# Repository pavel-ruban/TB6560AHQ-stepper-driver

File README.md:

#TB6560AHQ-stepper-driver
KiCAD project of stepper motor driver that is used to drive 1.6-1.7 A 2-phase stepper motors like NEMA-17 for CNC or 3D printers applications.

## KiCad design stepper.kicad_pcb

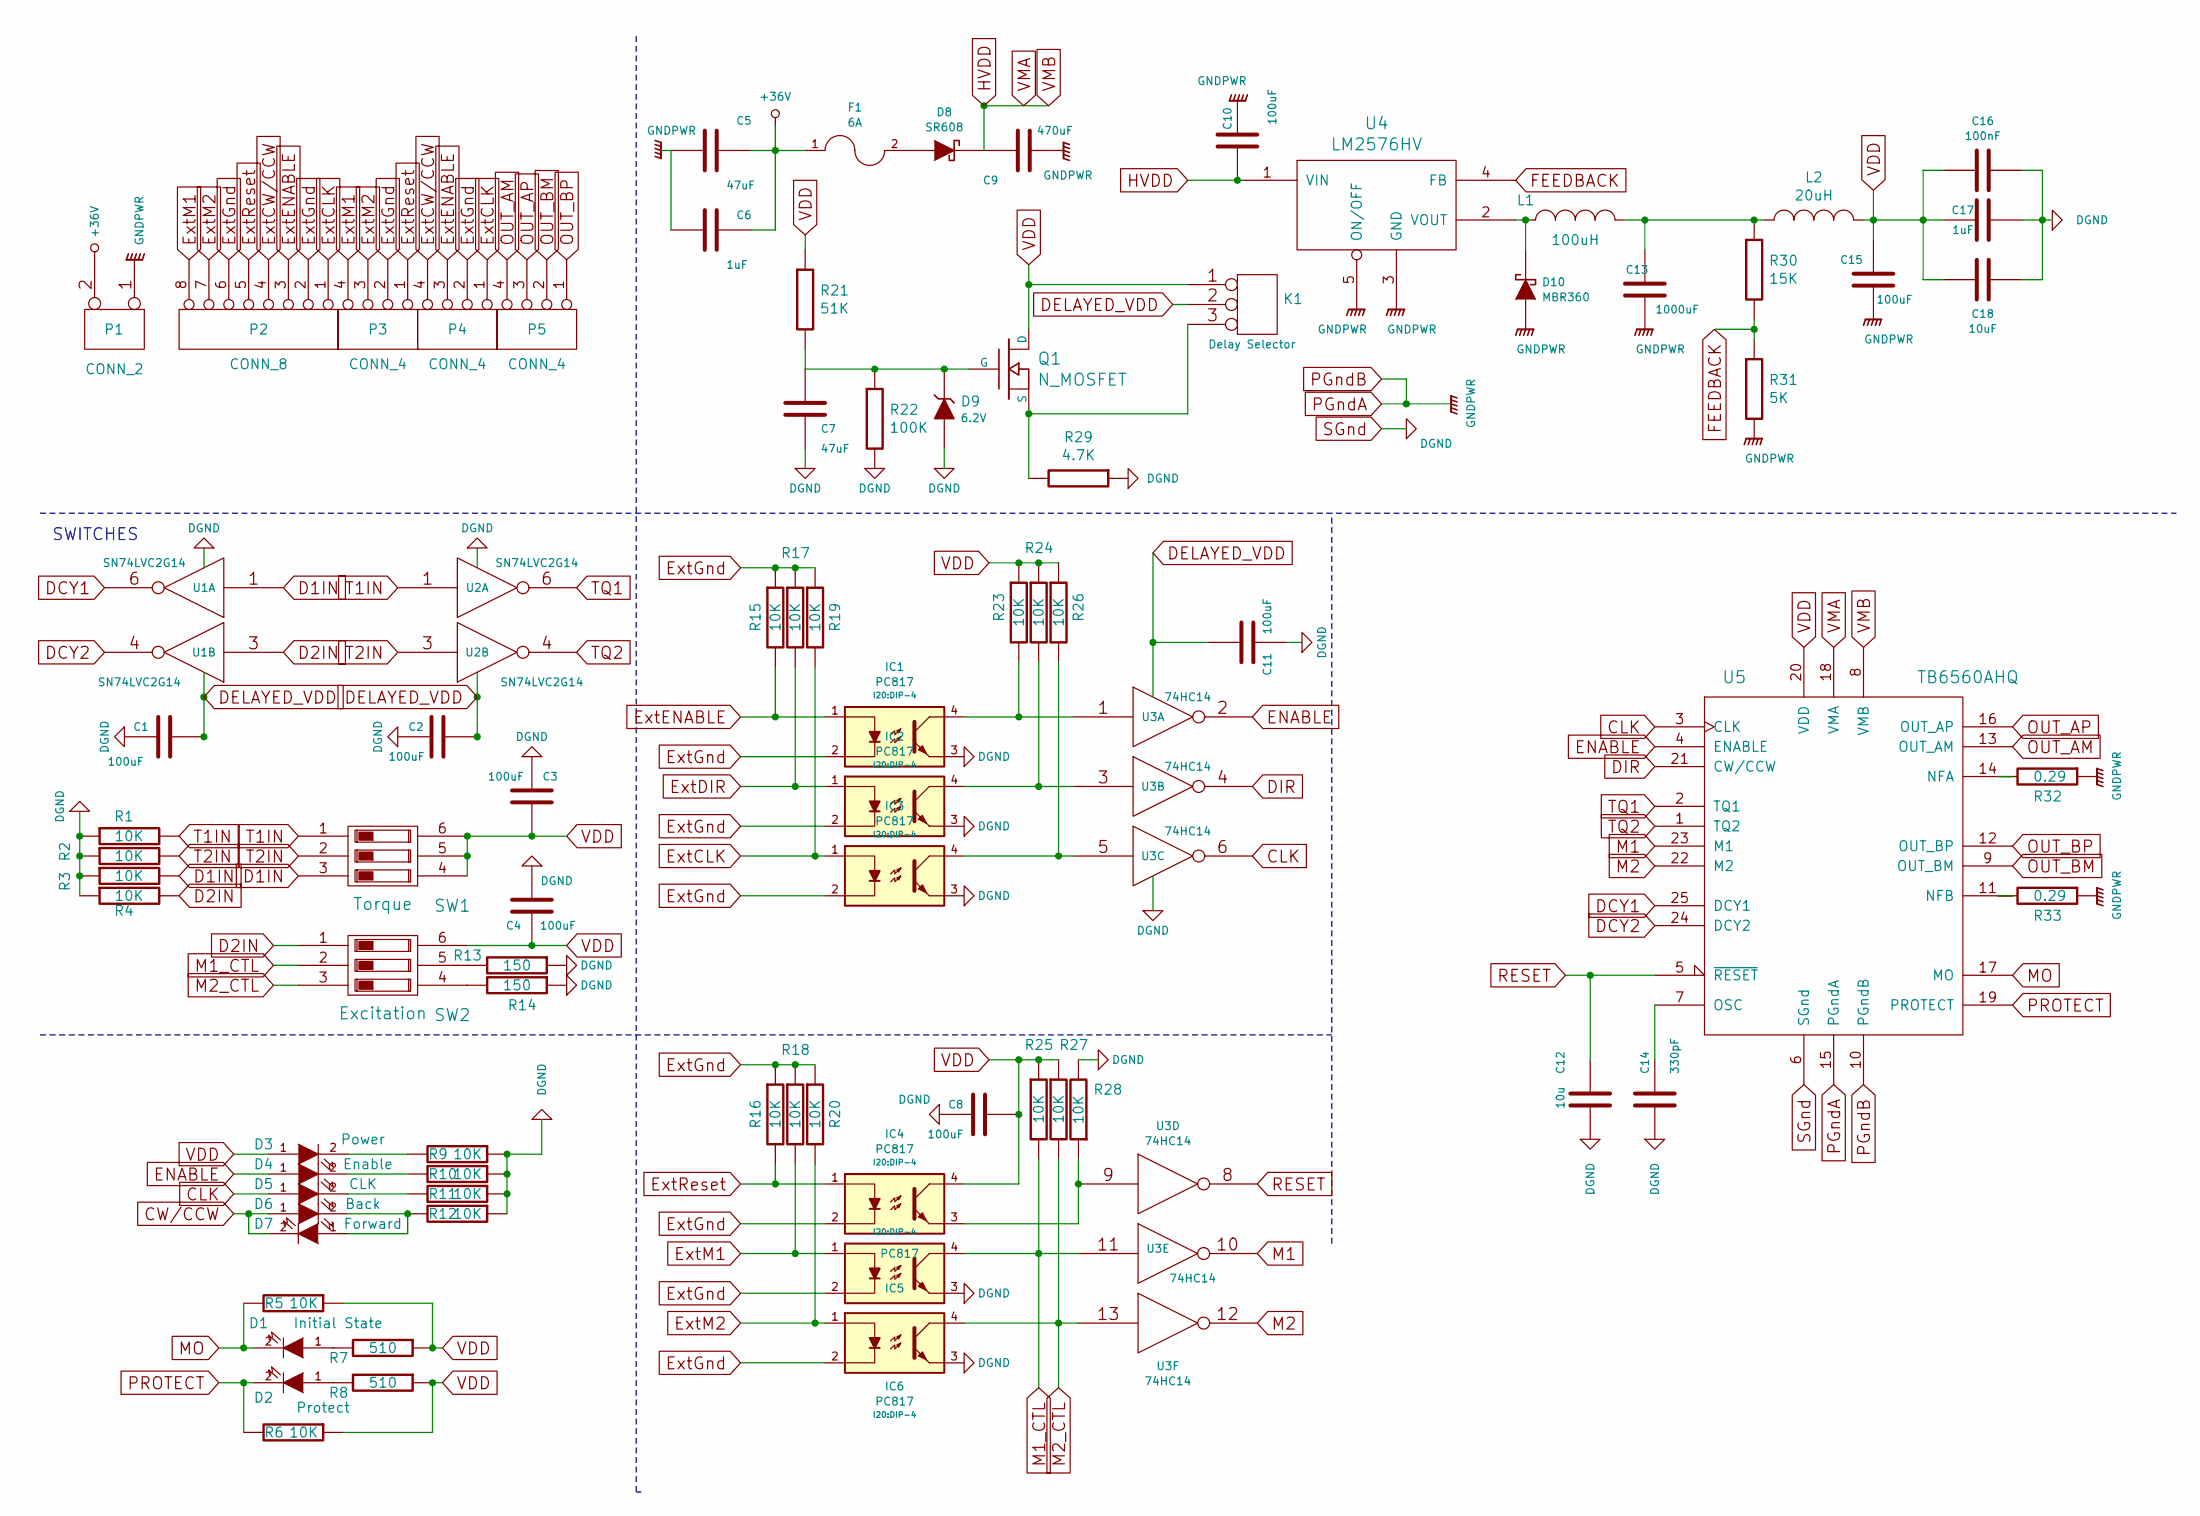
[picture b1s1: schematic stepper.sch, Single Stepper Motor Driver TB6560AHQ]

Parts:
C1, C2, C3, C4, C8, C11: 100uF; C_0805
C5, C7: 47uF; C_Radial_D6.3_L11.2_P2.5
C6: 1uF; C_Radial_D5_L11_P2.5
C9: 470uF; C_Radial_D10_L20_P5
C10, C15: 100uF; C_Radial_D8_L13_P3.8
C12: 10u; C_0805
C13: 1000uF; C_Radial_D10_L20_P5
C14: 330pF; C_0805
C16: 100nF; C_0805
C17: 1uF; C_0805
C18: 10uF; C_0805
D1: Initial State; LED_0805
D2: Protect; LED_0805
D3: Power; LED_0805
D4: Enable; LED_0805
D5: CLK; LED_0805
D6: Back; LED_0805
D7: Forward; LED_0805
D8: SR608; diode_r6
D9: 6.2V; MiniMELF_Standard
D10: MBR360; Diode_DO-201AD_Horizontal_RM15
F1: 6A; Fuseholder5x20_horiz_SemiClosed_Casing10x25mm
IC1, IC2, IC3, IC4, IC5, IC6: PC817; DIP-4
K1: Delay Selector; Pin_Header_Straight_1x03
L1: 100uH; L_Radial_D6.3_L11.2_P2.5
L2: 20uH; L_Radial_D6.3_L11.2_P2.5
P1: CONN_2; PhoenixContact_MSTBA-G_02x5.08mm_Angled
P2: CONN_8; Pin_Header_Straight_1x08
P3, P4: CONN_4; JST_XH_B04B-XH-A_04x2.50mm_Straight
P5: CONN_4; PhoenixContact_MSTBA-G_04x5.08mm_Angled
Q1: N_MOSFET; SOT-23
R1, R2, R3, R4, R5, R6, R9, R10, R11, R12, R15, R16, R17, R18, R19, R20, R23, R24, R25, R26, R27, R28: 10K; R_0805
R7, R8: 510; R_0805
R13, R14: 150; R_0805
R21: 51K; R_0805
R22: 100K; R_0805
R29: 4.7K; R_0805
R30: 15K; R_0805
R31: 5K; R_0805
R32, R33: 0.29; Resistor_Horizontal_RM15mm
SW1: Torque; DIPS-DS03
SW2: Excitation; DIPS-DS03
U1, U2: SN74LVC2G14; SOT-23-6
U3: 74HC14; SO14
U4: LM2576HV; Pentawatt_Neutral_Staggered_Verical_TO220-5-T05D
U5: TB6560AHQ; HZIP25_P_1_27_H

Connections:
+36V: C5.1, C6.1, F1.1, P1.2 (PM)
CLK: D5.1 (A), U3.6, U5.3 (CLK)
CW/CCW: D6.1 (A), D7.2 (K)
D1IN: R3.2, SW1.3, U1.1
D2IN: R4.2, SW2.1, U1.3
DCY1: U1.6, U5.25 (DCY1)
DCY2: U1.4, U5.24 (DCY2)
DELAYED_VDD: C1.2, C2.1, C11.2, K1.2 (PM), U1.5 (VCC), U2.5 (VCC), U3.14 (VCC)
DIR: U3.4, U5.21 (CW/CCW)
ENABLE: D4.1 (A), U3.2, U5.4 (ENABLE)
ExtCLK: IC3.1, P2.1, P4.1, R19.2
ExtCW/CCW: P2.4, P4.4
ExtDIR: IC2.1, R17.2
ExtENABLE: IC1.1, P2.3, P4.3, R15.2
ExtGnd: IC1.2, IC2.2, IC3.2, IC4.2, IC5.2, IC6.2, P2.2, P2.6, P3.2, P4.2, R15.1, R16.1, R17.1, R18.1, R19.1, R20.1
ExtM1: IC5.1, P2.8, P3.4, R18.2
ExtM2: IC6.1, P2.7, P3.3, R20.2
ExtReset: IC4.1, P2.5, P3.1, R16.2
FEEDBACK: R30.2, R31.1, U4.4 (FB)
HVDD: C9.1, C10.2, D8.2 (K), U4.1 (VIN), U5.8 (VMB), U5.18 (VMA)
M1: U3.10, U5.23 (M1)
M1_CTL: IC5.4, R25.2, SW2.2, U3.11
M2: U3.12, U5.22 (M2)
M2_CTL: IC6.4, R27.2, SW2.3, U3.13
MO: D1.2 (K), R5.2, U5.17 (MO)
unnamed: C7.2, D9.2 (K), Q1.1 (G), R21.2, R22.1
unnamed: C13.1, L1.2, L2.1, R30.1
unnamed: C14.1, U5.7 (OSC)
unnamed: D1.1 (A), R7.2
unnamed: D2.1 (A), R8.2
unnamed: D3.2 (K), R9.2
unnamed: D4.2 (K), R10.2
unnamed: D5.2 (K), R11.2
unnamed: D6.2 (K), D7.1 (A), R12.2
unnamed: D8.1 (A), F1.2
unnamed: D10.2 (K), L1.1, U4.2 (VOUT)
unnamed: IC1.4, R23.2, U3.1
unnamed: IC2.4, R24.2, U3.3
unnamed: IC3.4, R26.2, U3.5
unnamed: IC4.3, R28.1, U3.9
unnamed: K1.3, Q1.2 (S), R29.2
unnamed: R13.2, SW2.5
unnamed: R14.2, SW2.4
unnamed: R32.2, U5.14 (NFA)
unnamed: R33.2, U5.11 (NFB)
OUT_AM: P5.4, U5.13 (OUT_AM)
OUT_AP: P5.3, U5.16 (OUT_AP)
OUT_BM: P5.2, U5.9 (OUT_BM)
OUT_BP: P5.1, U5.12 (OUT_BP)
PGndA: C5.2, C6.2, C9.2, C10.1, C13.2, C15.2, D10.1 (A), P1.1, R31.2, R32.1, R33.1, U4.3 (GND), U4.5 (ON/OFF), U5.10 (PGndB), U5.15 (PGndA)
PROTECT: D2.2 (K), R6.2, U5.19 (PROTECT)
RESET: C12.1, U3.8, U5.5 (~RESET)
SGnd: C1.1, C2.2, C3.1, C4.2, C7.1, C8.1, C11.1, C12.2, C14.2, C16.2, C17.2, C18.2, D9.1 (A), IC1.3, IC2.3, IC3.3, IC5.3, IC6.3, R1.1, R2.1, R3.1, R4.1, R9.1, R10.1, R11.1, R12.1, R13.1, R14.1, R22.2, R28.2, R29.1, U1.2 (GND), U2.2 (GND), U3.7 (GND), U5.6 (SGnd)
T1IN: R1.2, SW1.1, U2.1
T2IN: R2.2, SW1.2, U2.3
TQ1: U2.6, U5.2 (TQ1)
TQ2: U2.4, U5.1 (TQ2)
VDD: C3.2, C4.1, C8.2, C15.1, C16.1, C17.1, C18.1, D3.1 (A), IC4.4, K1.1, L2.2, Q1.3 (D), R5.1, R6.1, R7.1, R8.1, R21.1, R23.1, R24.1, R25.1, R26.1, R27.1, SW1.4, SW1.5, SW1.6, SW2.6, U5.20 (VDD)

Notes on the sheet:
SWITCHES

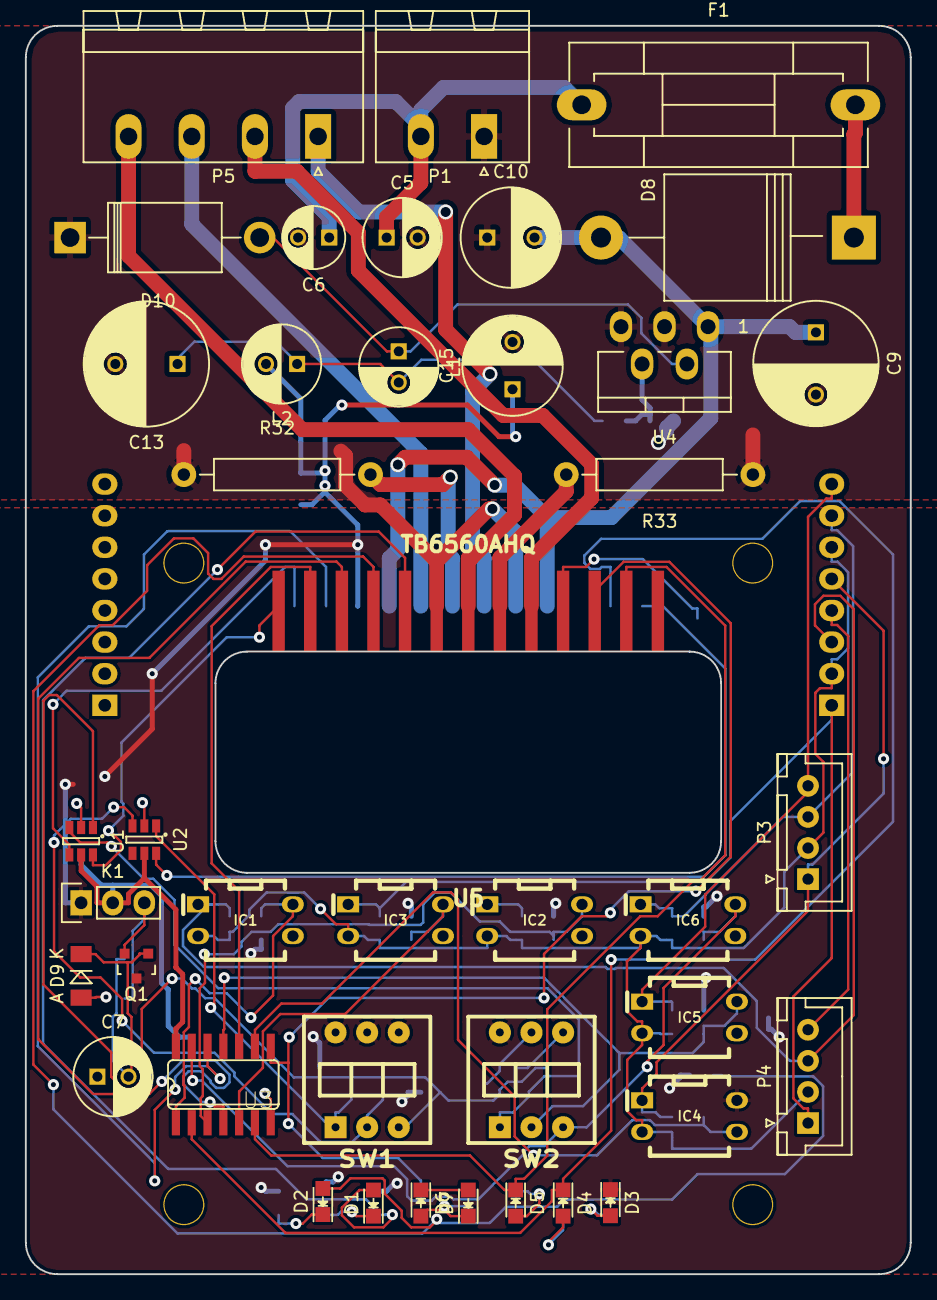
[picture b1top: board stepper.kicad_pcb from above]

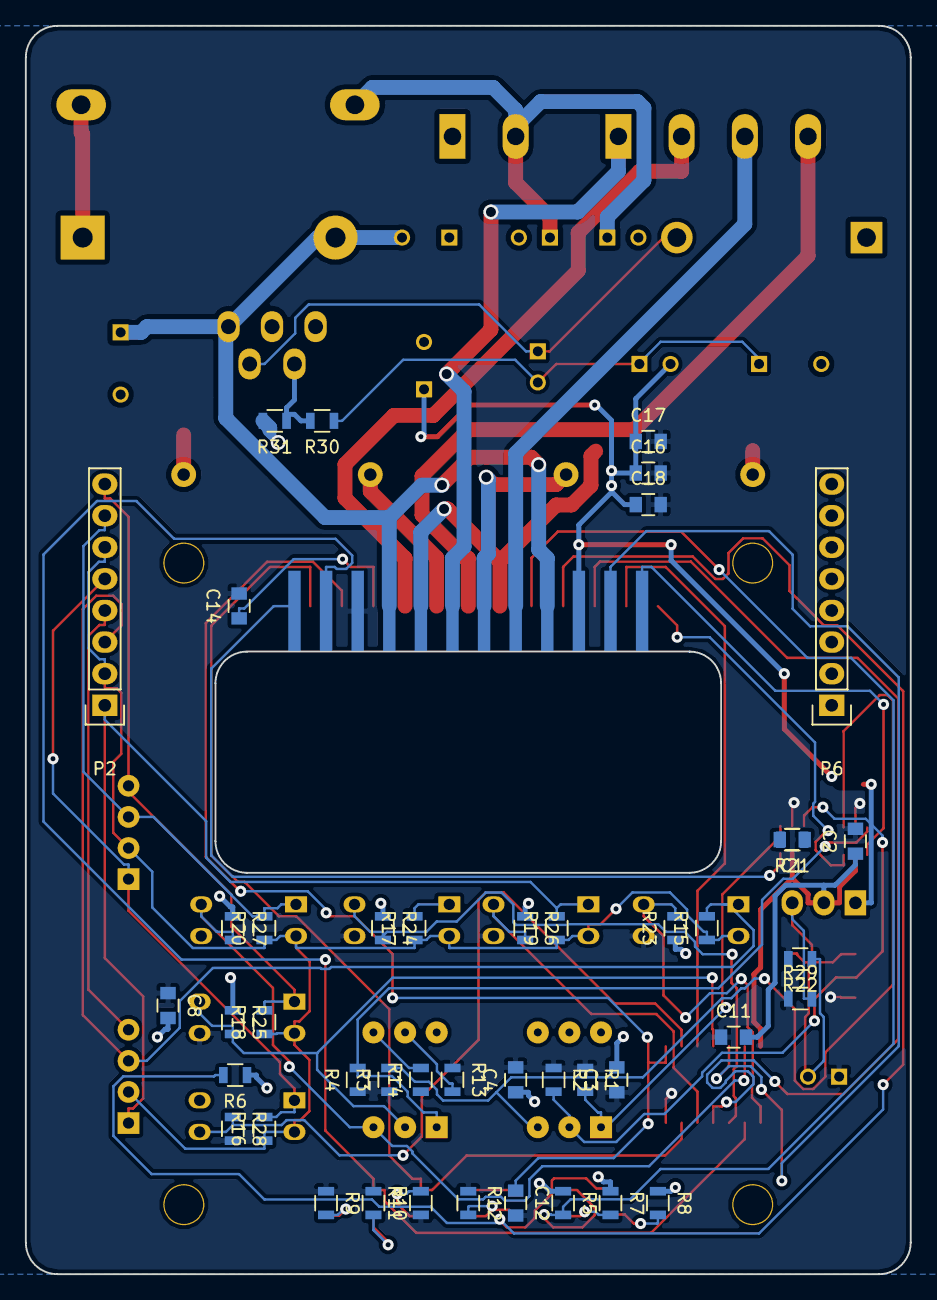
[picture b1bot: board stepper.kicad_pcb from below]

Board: 2 copper layers, 71.1 x 100.3 mm, 89 parts (44 on the bottom side), 58 nets.

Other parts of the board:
H1, H2, H3, H4: MountingHole_3.1mm
P6: CONN_8; Pin_Header_Straight_1x08

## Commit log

2016-11-07 make pcb control over version system
2016-11-07 add 3d model & screenshot
2016-11-08 adjust board, change lm2576 package
2016-11-08 adjust readme
2016-11-08 add screenshot
